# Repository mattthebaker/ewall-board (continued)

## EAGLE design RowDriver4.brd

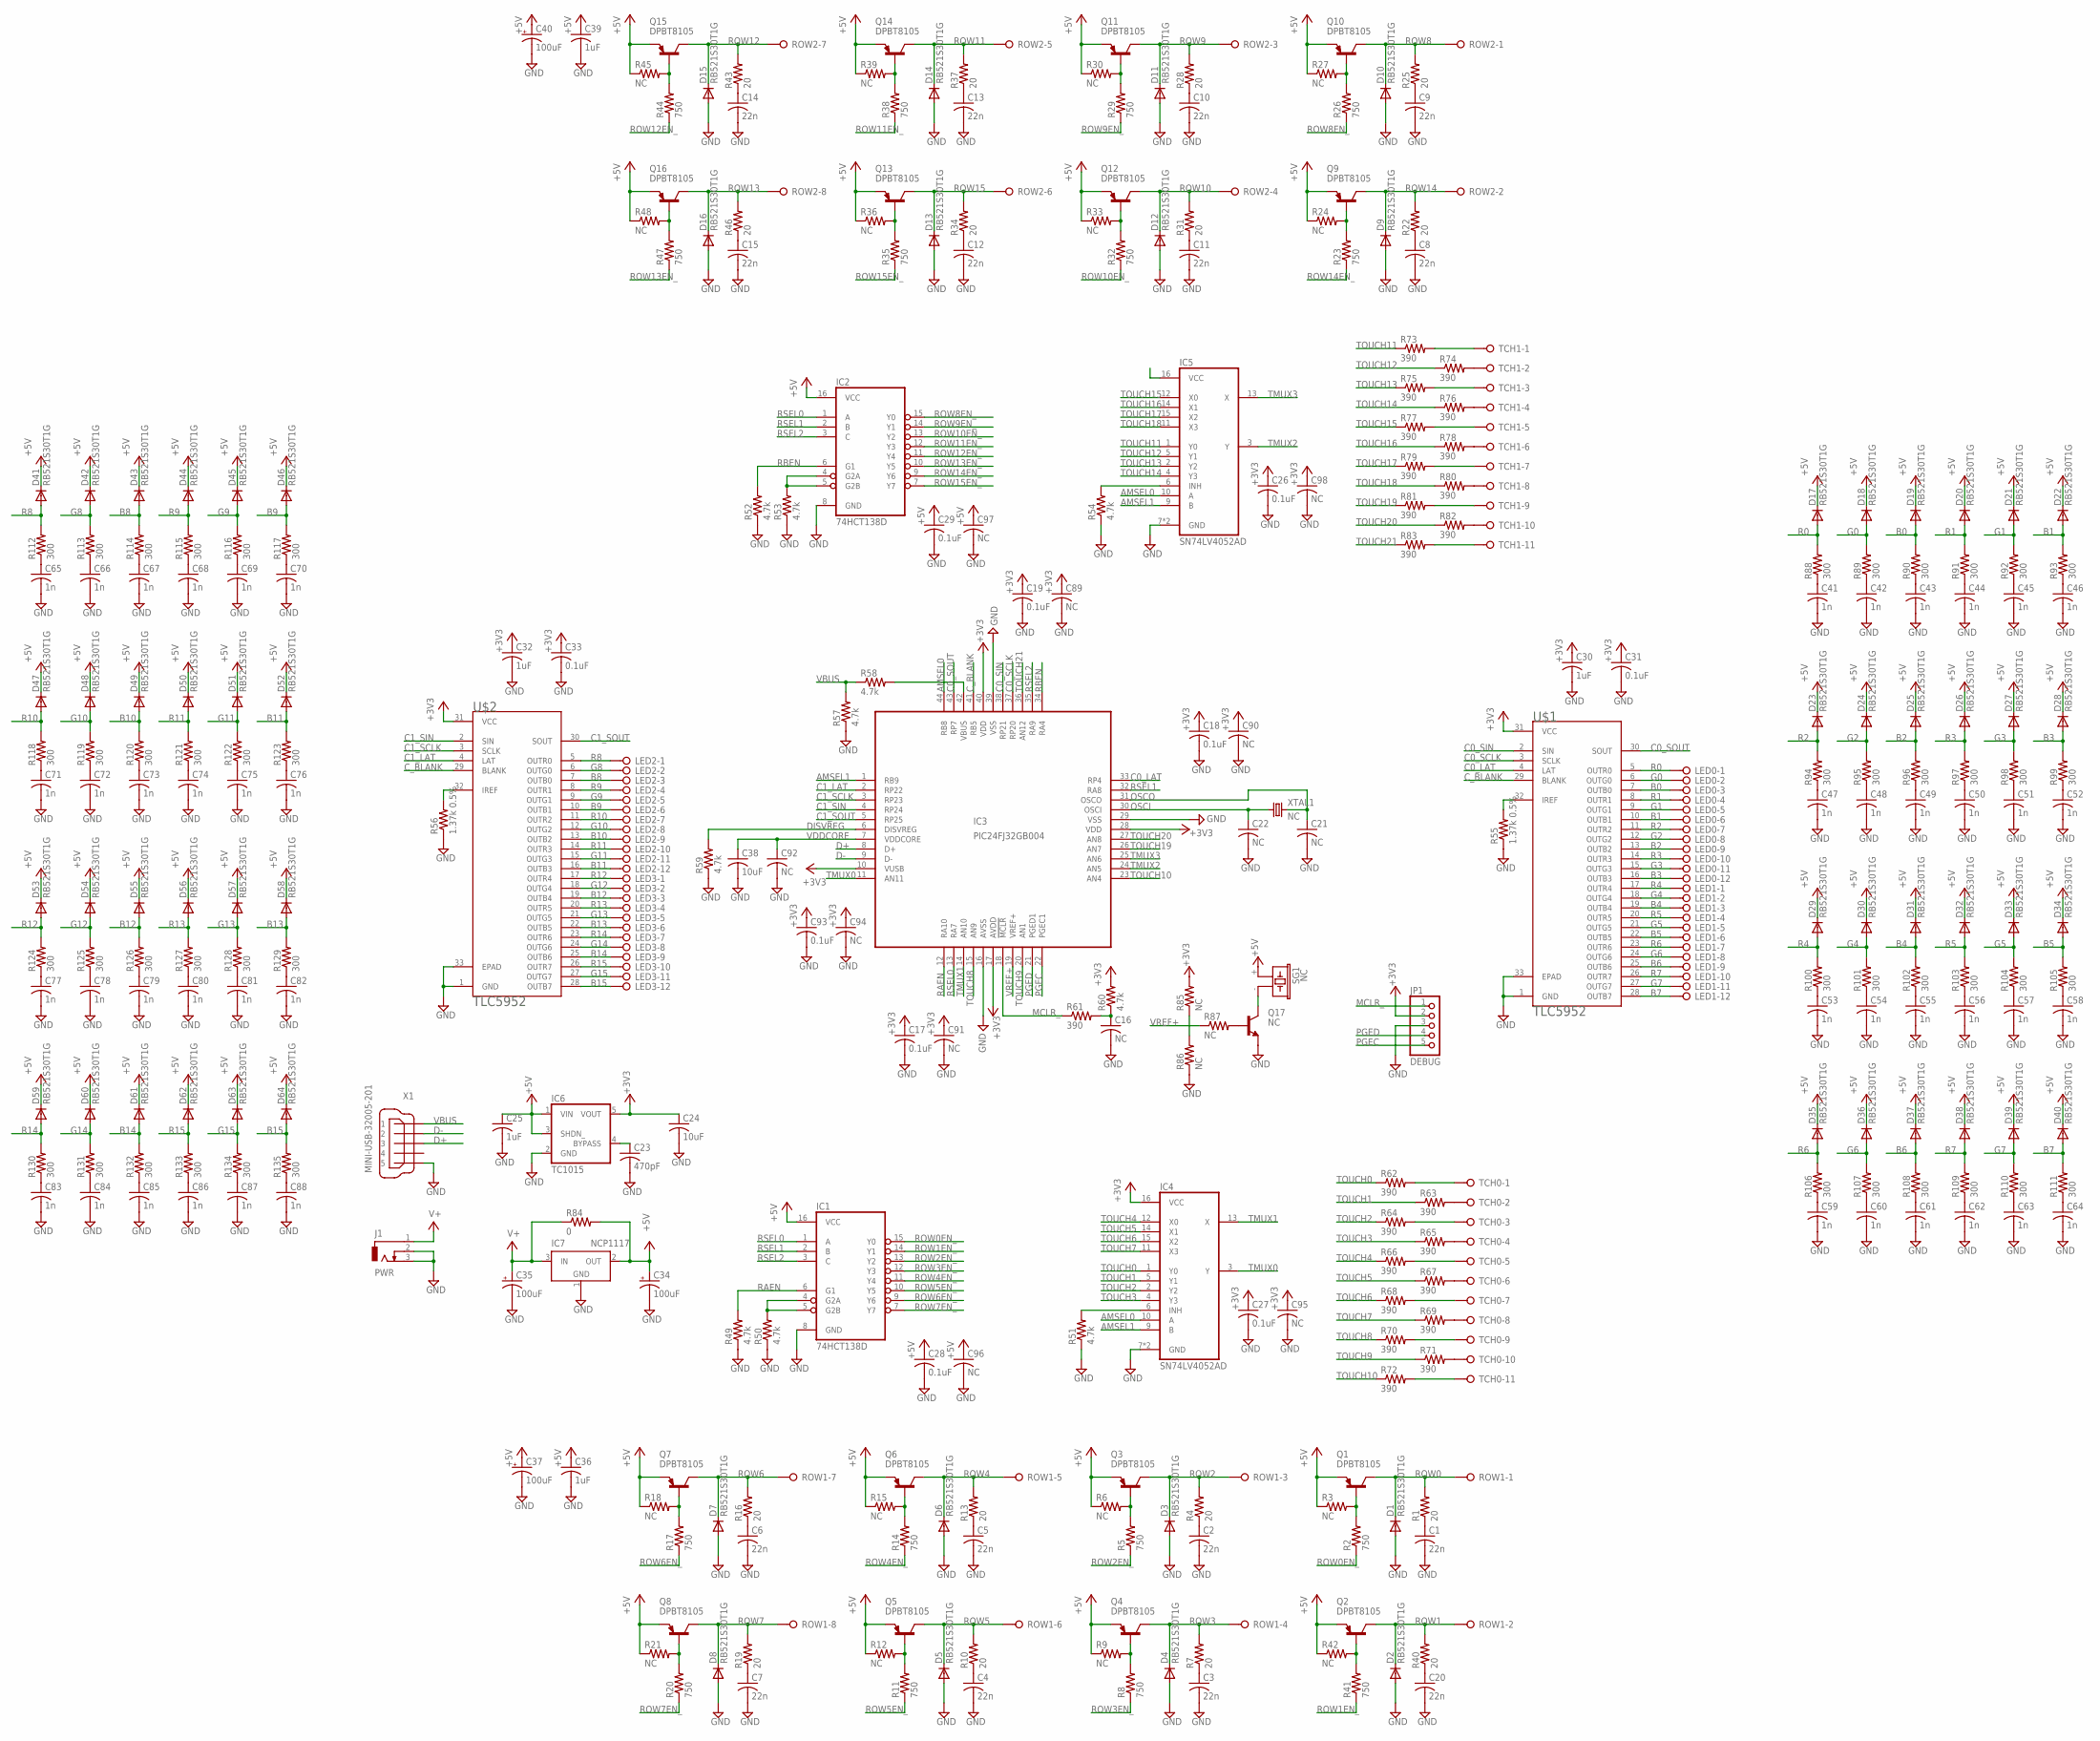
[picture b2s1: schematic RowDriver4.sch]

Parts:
C1, C2, C3, C4, C5, C6, C7, C8, C9, C10, C11, C12, C13, C14, C15, C20: 22n; C0603
C16, C21, C22, C89, C90, C91, C92, C94, C95, C96, C97, C98: NC; C0805
C17, C18, C19, C26, C27, C28, C29, C31, C33, C93: 0.1uF; C0805
C23: 470pF; C0805
C24, C38: 10uF; C1206K
C25, C30, C32, C36, C39: 1uF; C0805
C34, C35, C37, C40: 100uF; PANASONIC_D
C41, C42, C43, C44, C45, C46, C47, C48, C49, C50, C51, C52, C53, C54, C55, C56, C57, C58, C59, C60, C61, C62, C63, C64, C65, C66, C67, C68, C69, C70, C71, C72, C73, C74, C75, C76, C77, C78, C79, C80, C81, C82, C83, C84, C85, C86, C87, C88: 1n; C0805
D1, D2, D3, D4, D5, D6, D7, D8, D9, D10, D11, D12, D13, D14, D15, D16, D17, D18, D19, D20, D21, D22, D23, D24, D25, D26, D27, D28, D29, D30, D31, D32, D33, D34, D35, D36, D37, D38, D39, D40, D41, D42, D43, D44, D45, D46, D47, D48, D49, D50, D51, D52, D53, D54, D55, D56, D57, D58, D59, D60, D61, D62, D63, D64: RB521S30T1G; SOD523
IC1, IC2: 74HCT138D; SO16
IC3: PIC24FJ32GB004; TQFP44
IC4, IC5: SN74LV4052AD; SO16
IC6: TC1015; SOT23-5L
IC7: NCP1117; SOT223
J1: PWR; DCJ0303
JP1: DEBUG; 1X05/90
LED0, LED1, LED2, LED3: OSTVN12A150; OSTVN12
Q1, Q2, Q3, Q4, Q5, Q6, Q7, Q8, Q9, Q10, Q11, Q12, Q13, Q14, Q15, Q16: DPBT8105; SOT23
Q17: NC; SOT23-EBC
R1, R4, R7, R10, R13, R16, R19, R22, R25, R28, R31, R34, R37, R40, R43, R46: 20; R0603
R2, R5, R8, R11, R14, R17, R20, R23, R26, R29, R32, R35, R38, R41, R44, R47: 750; R0603
R3, R6, R9, R12, R15, R18, R21, R24, R27, R30, R33, R36, R39, R42, R45, R48: NC; R0603
R49, R50, R51, R52, R53, R54, R57, R58, R59, R60: 4.7k; R0805
R55, R56: 1.37k 0.5%; R0805
R61, R62, R63, R64, R65, R66, R67, R68, R69, R70, R71, R72, R73, R74, R75, R76, R77, R78, R79, R80, R81, R82, R83: 390; R0805
R84: 0; R0805
R85, R86, R87: NC; R0805
R88, R89, R90, R91, R92, R93, R94, R95, R96, R97, R98, R99, R100, R101, R102, R103, R104, R105, R106, R107, R108, R109, R110, R111, R112, R113, R114, R115, R116, R117, R118, R119, R120, R121, R122, R123, R124, R125, R126, R127, R128, R129, R130, R131, R132, R133, R134, R135: 300; R0805
ROW1, ROW2: OSTVN08A150; OSTVN08
SG1: NC; F/CM04P
TCH0, TCH1: OSTVN11A150; OSTVN11
U$1, U$2: TLC5952; HTSSOP-32POWERPAD
X1: MINI-USB-32005-201; 32005-201
XTAL1: NC; HC49UP

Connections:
+3V3: C17.1, C18.1, C19.1, C24.1, C26.1, C27.1, C30.1, C31.1, C32.1, C33.1, C89.1, C90.1, C91.1, C93.1, C94.1, C95.1, C98.1, IC3.10 (VUSB), IC3.17 (AVDD), IC3.28 (VDD), IC3.40 (VDD), IC4.16 (VCC), IC5.16 (VCC), IC6.5 (VOUT), JP1.2, R60.2, R85.2, U$1.31 (VCC), U$2.31 (VCC)
+5V: C25.1, C28.1, C29.1, C34.+, C36.1, C37.+, C39.1, C40.+, C96.1, C97.1, D17.C, D18.C, D19.C, D20.C, D21.C, D22.C, D23.C, D24.C, D25.C, D26.C, D27.C, D28.C, D29.C, D30.C, D31.C, D32.C, D33.C, D34.C, D35.C, D36.C, D37.C, D38.C, D39.C, D40.C, D41.C, D42.C, D43.C, D44.C, D45.C, D46.C, D47.C, D48.C, D49.C, D50.C, D51.C, D52.C, D53.C, D54.C, D55.C, D56.C, D57.C, D58.C, D59.C, D60.C, D61.C, D62.C, D63.C, D64.C, IC1.16 (VCC), IC2.16 (VCC), IC6.1 (VIN), IC6.3 (SHDN_), IC7.2 (OUT), Q1.2 (E), Q2.2 (E), Q3.2 (E), Q4.2 (E), Q5.2 (E), Q6.2 (E), Q7.2 (E), Q8.2 (E), Q9.2 (E), Q10.2 (E), Q11.2 (E), Q12.2 (E), Q13.2 (E), Q14.2 (E), Q15.2 (E), Q16.2 (E), R3.1, R6.1, R9.1, R12.1, R15.1, R18.1, R21.1, R24.1, R27.1, R30.1, R33.1, R36.1, R39.1, R42.1, R45.1, R48.1, R84.2, SG1.+ (1)
AMSEL0: IC3.44 (RB8), IC4.10 (A), IC5.10 (A)
AMSEL1: IC3.1 (RB9), IC4.9 (B), IC5.9 (B)
B0: D19.A, LED0.3, R90.2, U$1.7 (OUTB0)
B1: D22.A, LED0.6, R93.2, U$1.10 (OUTB1)
B2: D25.A, LED0.9, R96.2, U$1.13 (OUTB2)
B3: D28.A, LED0.12, R99.2, U$1.16 (OUTB3)
B4: D31.A, LED1.3, R102.2, U$1.19 (OUTB4)
B5: D34.A, LED1.6, R105.2, U$1.22 (OUTB5)
B6: D37.A, LED1.9, R108.2, U$1.25 (OUTB6)
B7: D40.A, LED1.12, R111.2, U$1.28 (OUTB7)
B8: D43.A, LED2.3, R114.2, U$2.7 (OUTB0)
B9: D46.A, LED2.6, R117.2, U$2.10 (OUTB1)
B10: D49.A, LED2.9, R120.2, U$2.13 (OUTB2)
B11: D52.A, LED2.12, R123.2, U$2.16 (OUTB3)
B12: D55.A, LED3.3, R126.2, U$2.19 (OUTB4)
B13: D58.A, LED3.6, R129.2, U$2.22 (OUTB5)
B14: D61.A, LED3.9, R132.2, U$2.25 (OUTB6)
B15: D64.A, LED3.12, R135.2, U$2.28 (OUTB7)
C0_LAT: IC3.33 (RP4), U$1.4 (LAT)
C0_SCLK: IC3.37 (RP20), U$1.3 (SCLK)
C0_SIN: IC3.38 (RP21), U$1.2 (SIN)
C0_SOUT: IC3.43 (RP7), U$1.30 (SOUT)
C1_LAT: IC3.2 (RP22), U$2.4 (LAT)
C1_SCLK: IC3.3 (RP23), U$2.3 (SCLK)
C1_SIN: IC3.4 (RP24), U$2.2 (SIN)
C1_SOUT: IC3.5 (RP25), U$2.30 (SOUT)
CAIREF: R55.2, U$1.32 (IREF)
CAIREF1: R56.2, U$2.32 (IREF)
C_BLANK: IC3.41 (RB5), U$1.29 (BLANK), U$2.29 (BLANK)
D+: IC3.8 (D+), X1.3
D-: IC3.9 (D-), X1.2
DISVREG: IC3.6 (DISVREG), R59.2
G0: D18.A, LED0.2, R89.2, U$1.6 (OUTG0)
G1: D21.A, LED0.5, R92.2, U$1.9 (OUTG1)
G2: D24.A, LED0.8, R95.2, U$1.12 (OUTG2)
G3: D27.A, LED0.11, R98.2, U$1.15 (OUTG3)
G4: D30.A, LED1.2, R101.2, U$1.18 (OUTG4)
G5: D33.A, LED1.5, R104.2, U$1.21 (OUTG5)
G6: D36.A, LED1.8, R107.2, U$1.24 (OUTG6)
G7: D39.A, LED1.11, R110.2, U$1.27 (OUTG7)
G8: D42.A, LED2.2, R113.2, U$2.6 (OUTG0)
G9: D45.A, LED2.5, R116.2, U$2.9 (OUTG1)
G10: D48.A, LED2.8, R119.2, U$2.12 (OUTG2)
G11: D51.A, LED2.11, R122.2, U$2.15 (OUTG3)
G12: D54.A, LED3.2, R125.2, U$2.18 (OUTG4)
G13: D57.A, LED3.5, R128.2, U$2.21 (OUTG5)
G14: D60.A, LED3.8, R131.2, U$2.24 (OUTG6)
G15: D63.A, LED3.11, R134.2, U$2.27 (OUTG7)
GND: C1.2, C2.2, C3.2, C4.2, C5.2, C6.2, C7.2, C8.2, C9.2, C10.2, C11.2, C12.2, C13.2, C14.2, C15.2, C16.2, C17.2, C18.2, C19.2, C20.2, C21.2, C22.2, C23.2, C24.2, C25.2, C26.2, C27.2, C28.2, C29.2, C30.2, C31.2, C32.2, C33.2, C34.-, C35.-, C36.2, C37.-, C38.2, C39.2, C40.-, C41.2, C42.2, C43.2, C44.2, C45.2, C46.2, C47.2, C48.2, C49.2, C50.2, C51.2, C52.2, C53.2, C54.2, C55.2, C56.2, C57.2, C58.2, C59.2, C60.2, C61.2, C62.2, C63.2, C64.2, C65.2, C66.2, C67.2, C68.2, C69.2, C70.2, C71.2, C72.2, C73.2, C74.2, C75.2, C76.2, C77.2, C78.2, C79.2, C80.2, C81.2, C82.2, C83.2, C84.2, C85.2, C86.2, C87.2, C88.2, C89.2, C90.2, C91.2, C92.2, C93.2, C94.2, C95.2, C96.2, C97.2, C98.2, D1.A, D2.A, D3.A, D4.A, D5.A, D6.A, D7.A, D8.A, D9.A, D10.A, D11.A, D12.A, D13.A, D14.A, D15.A, D16.A, IC1.8 (GND), IC2.8 (GND), IC3.16 (AVSS), IC3.29 (VSS), IC3.39 (VSS), IC4.7 (GND), IC4.8 (GND), IC5.7 (GND), IC5.8 (GND), IC6.2 (GND), IC7.1 (GND), IC7.4 (GND), J1.2, J1.3, JP1.3, Q17.E, R49.1, R50.1, R51.1, R52.1, R53.1, R54.1, R55.1, R56.1, R57.1, R59.1, R86.1, U$1.1 (GND), U$1.33 (EPAD), U$2.1 (GND), U$2.33 (EPAD), X1.5
MCLR_: IC3.18 (!MCLR), JP1.1, R61.1
unnamed: Q1.1 (B), R2.2, R3.2
unnamed: C1.1, R1.1
unnamed: Q3.1 (B), R5.2, R6.2
unnamed: C2.1, R4.1
unnamed: Q4.1 (B), R8.2, R9.2
unnamed: C3.1, R7.1
unnamed: Q5.1 (B), R11.2, R12.2
unnamed: C4.1, R10.1
unnamed: Q6.1 (B), R14.2, R15.2
unnamed: C5.1, R13.1
unnamed: Q7.1 (B), R17.2, R18.2
unnamed: C6.1, R16.1
unnamed: Q8.1 (B), R20.2, R21.2
unnamed: C7.1, R19.1
unnamed: Q9.1 (B), R23.2, R24.2
unnamed: C8.1, R22.1
unnamed: Q10.1 (B), R26.2, R27.2
unnamed: C9.1, R25.1
unnamed: Q11.1 (B), R29.2, R30.2
unnamed: C10.1, R28.1
unnamed: Q12.1 (B), R32.2, R33.2
unnamed: C11.1, R31.1
unnamed: Q13.1 (B), R35.2, R36.2
unnamed: C12.1, R34.1
unnamed: Q14.1 (B), R38.2, R39.2
unnamed: C13.1, R37.1
unnamed: Q15.1 (B), R44.2, R45.2
unnamed: C14.1, R43.1
unnamed: Q16.1 (B), R47.2, R48.2
unnamed: C15.1, R46.1
unnamed: Q2.1 (B), R41.2, R42.2
unnamed: C20.1, R40.1
unnamed: IC1.4 (G2A), IC1.5 (G2B), R50.2
unnamed: IC4.6 (INH), R51.2
unnamed: IC2.4 (G2A), IC2.5 (G2B), R53.2
unnamed: IC5.6 (INH), R54.2
unnamed: IC3.42 (VBUS), R58.2
unnamed: C16.1, R60.1, R61.2
unnamed: R62.2, TCH0.1
unnamed: R63.2, TCH0.2
unnamed: R64.2, TCH0.3
unnamed: R65.2, TCH0.4
unnamed: R66.2, TCH0.5
unnamed: R67.2, TCH0.6
unnamed: R68.2, TCH0.7
unnamed: R69.2, TCH0.8
unnamed: R70.2, TCH0.9
unnamed: R71.2, TCH0.10
unnamed: R72.2, TCH0.11
unnamed: R74.2, TCH1.2
unnamed: R76.2, TCH1.4
unnamed: R78.2, TCH1.6
unnamed: R80.2, TCH1.8
unnamed: R82.2, TCH1.10
unnamed: R73.2, TCH1.1
unnamed: R75.2, TCH1.3
unnamed: R77.2, TCH1.5
unnamed: R79.2, TCH1.7
unnamed: R81.2, TCH1.9
unnamed: R83.2, TCH1.11
unnamed: C23.1, IC6.4 (BYPASS)
unnamed: R85.1, R86.2
unnamed: Q17.B, R87.2
unnamed: Q17.C, SG1.- (2)
unnamed: C41.1, R88.1
unnamed: C42.1, R89.1
unnamed: C43.1, R90.1
unnamed: C44.1, R91.1
unnamed: C45.1, R92.1
unnamed: C46.1, R93.1
unnamed: C47.1, R94.1
unnamed: C48.1, R95.1
unnamed: C49.1, R96.1
unnamed: C50.1, R97.1
unnamed: C51.1, R98.1
unnamed: C52.1, R99.1
unnamed: C53.1, R100.1
unnamed: C54.1, R101.1
unnamed: C55.1, R102.1
unnamed: C56.1, R103.1
unnamed: C57.1, R104.1
unnamed: C58.1, R105.1
unnamed: C59.1, R106.1
unnamed: C60.1, R107.1
unnamed: C61.1, R108.1
unnamed: C62.1, R109.1
unnamed: C63.1, R110.1
unnamed: C64.1, R111.1
unnamed: C65.1, R112.1
unnamed: C66.1, R113.1
unnamed: C67.1, R114.1
unnamed: C68.1, R115.1
unnamed: C69.1, R116.1
unnamed: C70.1, R117.1
unnamed: C71.1, R118.1
unnamed: C72.1, R119.1
unnamed: C73.1, R120.1
unnamed: C74.1, R121.1
unnamed: C75.1, R122.1
unnamed: C76.1, R123.1
unnamed: C77.1, R124.1
unnamed: C78.1, R125.1
unnamed: C79.1, R126.1
unnamed: C80.1, R127.1
unnamed: C81.1, R128.1
unnamed: C82.1, R129.1
unnamed: C83.1, R130.1
unnamed: C84.1, R131.1
unnamed: C85.1, R132.1
unnamed: C86.1, R133.1
unnamed: C87.1, R134.1
unnamed: C88.1, R135.1
OSCI: C22.1, IC3.30 (OSCI), XTAL1.1
OSCO: C21.1, IC3.31 (OSCO), XTAL1.2
PGEC: IC3.22 (PGEC1), JP1.5
PGED: IC3.21 (PGED1), JP1.4
R0: D17.A, LED0.1, R88.2, U$1.5 (OUTR0)
R1: D20.A, LED0.4, R91.2, U$1.8 (OUTR1)
R2: D23.A, LED0.7, R94.2, U$1.11 (OUTR2)
R3: D26.A, LED0.10, R97.2, U$1.14 (OUTR3)
R4: D29.A, LED1.1, R100.2, U$1.17 (OUTR4)
R5: D32.A, LED1.4, R103.2, U$1.20 (OUTR5)
R6: D35.A, LED1.7, R106.2, U$1.23 (OUTR6)
R7: D38.A, LED1.10, R109.2, U$1.26 (OUTR7)
R8: D41.A, LED2.1, R112.2, U$2.5 (OUTR0)
R9: D44.A, LED2.4, R115.2, U$2.8 (OUTR1)
R10: D47.A, LED2.7, R118.2, U$2.11 (OUTR2)
R11: D50.A, LED2.10, R121.2, U$2.14 (OUTR3)
R12: D53.A, LED3.1, R124.2, U$2.17 (OUTR4)
R13: D56.A, LED3.4, R127.2, U$2.20 (OUTR5)
R14: D59.A, LED3.7, R130.2, U$2.23 (OUTR6)
R15: D62.A, LED3.10, R133.2, U$2.26 (OUTR7)
RAEN: IC1.6 (G1), IC3.12 (RA10), R49.2
RBEN: IC2.6 (G1), IC3.34 (RA4), R52.2
ROW0: D1.C, Q1.3 (C), R1.2, ROW1.1
ROW0EN_: IC1.15 (Y0), R2.1
ROW1: D2.C, Q2.3 (C), R40.2, ROW1.2
ROW1EN_: IC1.14 (Y1), R41.1
ROW2: D3.C, Q3.3 (C), R4.2, ROW1.3
ROW2EN_: IC1.13 (Y2), R5.1
ROW3: D4.C, Q4.3 (C), R7.2, ROW1.4
ROW3EN_: IC1.12 (Y3), R8.1
ROW4: D6.C, Q6.3 (C), R13.2, ROW1.5
ROW4EN_: IC1.11 (Y4), R14.1
ROW5: D5.C, Q5.3 (C), R10.2, ROW1.6
ROW5EN_: IC1.10 (Y5), R11.1
ROW6: D7.C, Q7.3 (C), R16.2, ROW1.7
ROW6EN_: IC1.9 (Y6), R17.1
ROW7: D8.C, Q8.3 (C), R19.2, ROW1.8
ROW7EN_: IC1.7 (Y7), R20.1
ROW8: D10.C, Q10.3 (C), R25.2, ROW2.1
ROW8EN_: IC2.15 (Y0), R26.1
ROW9: D11.C, Q11.3 (C), R28.2, ROW2.3
ROW9EN_: IC2.14 (Y1), R29.1
ROW10: D12.C, Q12.3 (C), R31.2, ROW2.4
ROW10EN_: IC2.13 (Y2), R32.1
ROW11: D14.C, Q14.3 (C), R37.2, ROW2.5
ROW11EN_: IC2.12 (Y3), R38.1
ROW12: D15.C, Q15.3 (C), R43.2, ROW2.7
ROW12EN_: IC2.11 (Y4), R44.1
ROW13: D16.C, Q16.3 (C), R46.2, ROW2.8
ROW13EN_: IC2.10 (Y5), R47.1
ROW14: D9.C, Q9.3 (C), R22.2, ROW2.2
ROW14EN_: IC2.9 (Y6), R23.1
ROW15: D13.C, Q13.3 (C), R34.2, ROW2.6
ROW15EN_: IC2.7 (Y7), R35.1
RSEL0: IC1.1 (A), IC2.1 (A), IC3.13 (RA7)
RSEL1: IC1.2 (B), IC2.2 (B), IC3.32 (RA8)
RSEL2: IC1.3 (C), IC2.3 (C), IC3.35 (RA9)
TMUX0: IC3.11 (AN11), IC4.3 (Y)
TMUX1: IC3.14 (AN10), IC4.13 (X)
TMUX2: IC3.24 (AN5), IC5.3 (Y)
TMUX3: IC3.25 (AN6), IC5.13 (X)
TOUCH0: IC4.1 (Y0), R62.1
TOUCH1: IC4.5 (Y1), R63.1
TOUCH2: IC4.2 (Y2), R64.1
TOUCH3: IC4.4 (Y3), R65.1
TOUCH4: IC4.12 (X0), R66.1
TOUCH5: IC4.14 (X1), R67.1
TOUCH6: IC4.15 (X2), R68.1
TOUCH7: IC4.11 (X3), R69.1
TOUCH8: IC3.15 (AN9), R70.1
TOUCH9: IC3.20 (AN1), R71.1
TOUCH10: IC3.23 (AN4), R72.1
TOUCH11: IC5.1 (Y0), R73.1
TOUCH12: IC5.5 (Y1), R74.1
TOUCH13: IC5.2 (Y2), R75.1
TOUCH14: IC5.4 (Y3), R76.1
TOUCH15: IC5.12 (X0), R77.1
TOUCH16: IC5.14 (X1), R78.1
TOUCH17: IC5.15 (X2), R79.1
TOUCH18: IC5.11 (X3), R80.1
TOUCH19: IC3.26 (AN7), R81.1
TOUCH20: IC3.27 (AN8), R82.1
TOUCH21: IC3.36 (AN12), R83.1
V+: C35.+, IC7.3 (IN), J1.1, R84.1
VBUS: R57.2, R58.1, X1.1
VDDCORE: C38.1, C92.1, IC3.7 (VDDCORE)
VREF+: IC3.19 (VREF+), R87.1

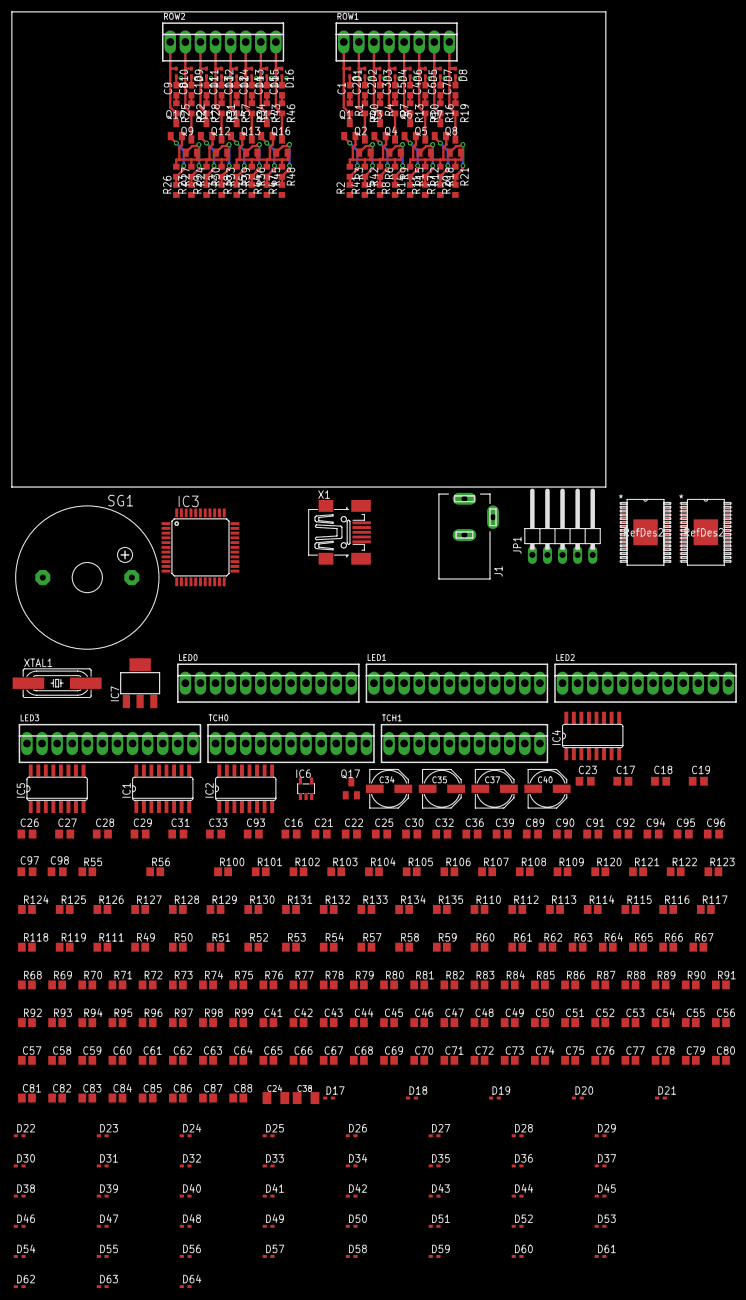
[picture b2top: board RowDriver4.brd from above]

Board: 2 copper layers, 100.0 x 88.6 mm, 336 parts (0 on the bottom side), 251 nets.

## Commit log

2012-12-08 Added board files from local copy.
2012-12-26 Created separate schematics for Row and Column Driver circuits. Added arrayed row and column noise filtering circuits. Added decoupling caps for ICs. Added voltage regulators for 3.3 and 5v rails. Ad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
2013-01-01 Implemented full schematic and filled in component values. Schematic is 95% complete, layout may commence.
2013-01-06 Added footprint for LED driver: HTSSOP-32 PowerPad. Cleaned up unnecessary symbols, packages, and devices in library.
2013-01-07 Cleaned up library further. Picked PNP row switch. Converted placeholder RC values with standard values. Added some part documentation.
2013-01-07 Added terminal block documentation.
2013-01-09 Added datasheets for many components.
2013-01-09 Cleaned up all ERC errors in the schematic.
2013-01-10 Created initial main board. Created layout for row driver, and tiled it. The new board and schematic files for the row driver are intermediate steps.
2013-01-11 Iterated through a few possible board floorplans. Routing will be incredibly tight, but I thought of a few possibilities that ease those concerns.
2013-01-12 Completed most of the column driver routing.
2013-01-14 Completed row/column routing.
2013-01-19 Made progress on layout.
2013-01-20 Completed routing of all circuit board elements. Created ground fills, and stitched everything together. Need to review sensitive signal coupling and review decoupling paths. Need to verify footprint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
2013-01-20 Cleaned up floating ratsnest wires. Cleaned up DRC Errors. Need to check DRC with SEEED's rule set.
2013-01-21 DRC Passed with SEEED Rules. Added extra input to touch connector because 11-socket parts aren't available. Fixed 5v regulator pin out, and added PCB heat sink. Messed with device attributes for manu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
2013-01-21 Increased LED Driver power pad to recommended specs. Exported BOM, massaged, and identified parts at digikey.csv. Setup a Digikey BOM.
2013-01-22 Optimized LED Driver footprint and paste mask to match the datasheet. Optimized a few signal routes to reduce noise coupling. Reviewed trace coupling on sensitive nodes. (Layout is good).
2013-01-23 Improved 5v power routing for etching concerns.
2013-01-24 Added Logos to board. Cleaned up part names on board. Fixed LED driver part name.
2013-01-24 Added gerber files to repository.
2013-03-25 Updated NC status on column clamp diodes. Added new datasheet.
